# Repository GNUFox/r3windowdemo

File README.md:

# Realraum Window Demo

Responsive VGA based Demo for the Realraum Window front

## TL;DR
 * Detect people walking by through Radar Sensors (10 GHz)
 * Enable Screens only when so. is walking by to reduce power consumption
 * Use Raspberry Pi Pico(s) to run VGA based demos / intros
 * Maybe also use normal Raspberry Pi (1,2, etc.) to display other info

## TODO

- [ ] Pico <-> VGA Adapter
- [ ] Radar detector (switch power for screens)
- [ ] Normal raspberry with HDMI <-> VGA for other info

## Sources

Pico KiCAD symbol / footprint: https://forum.kicad.info/t/are-there-pi-pico-library-files-available-for-kicad-6/35844

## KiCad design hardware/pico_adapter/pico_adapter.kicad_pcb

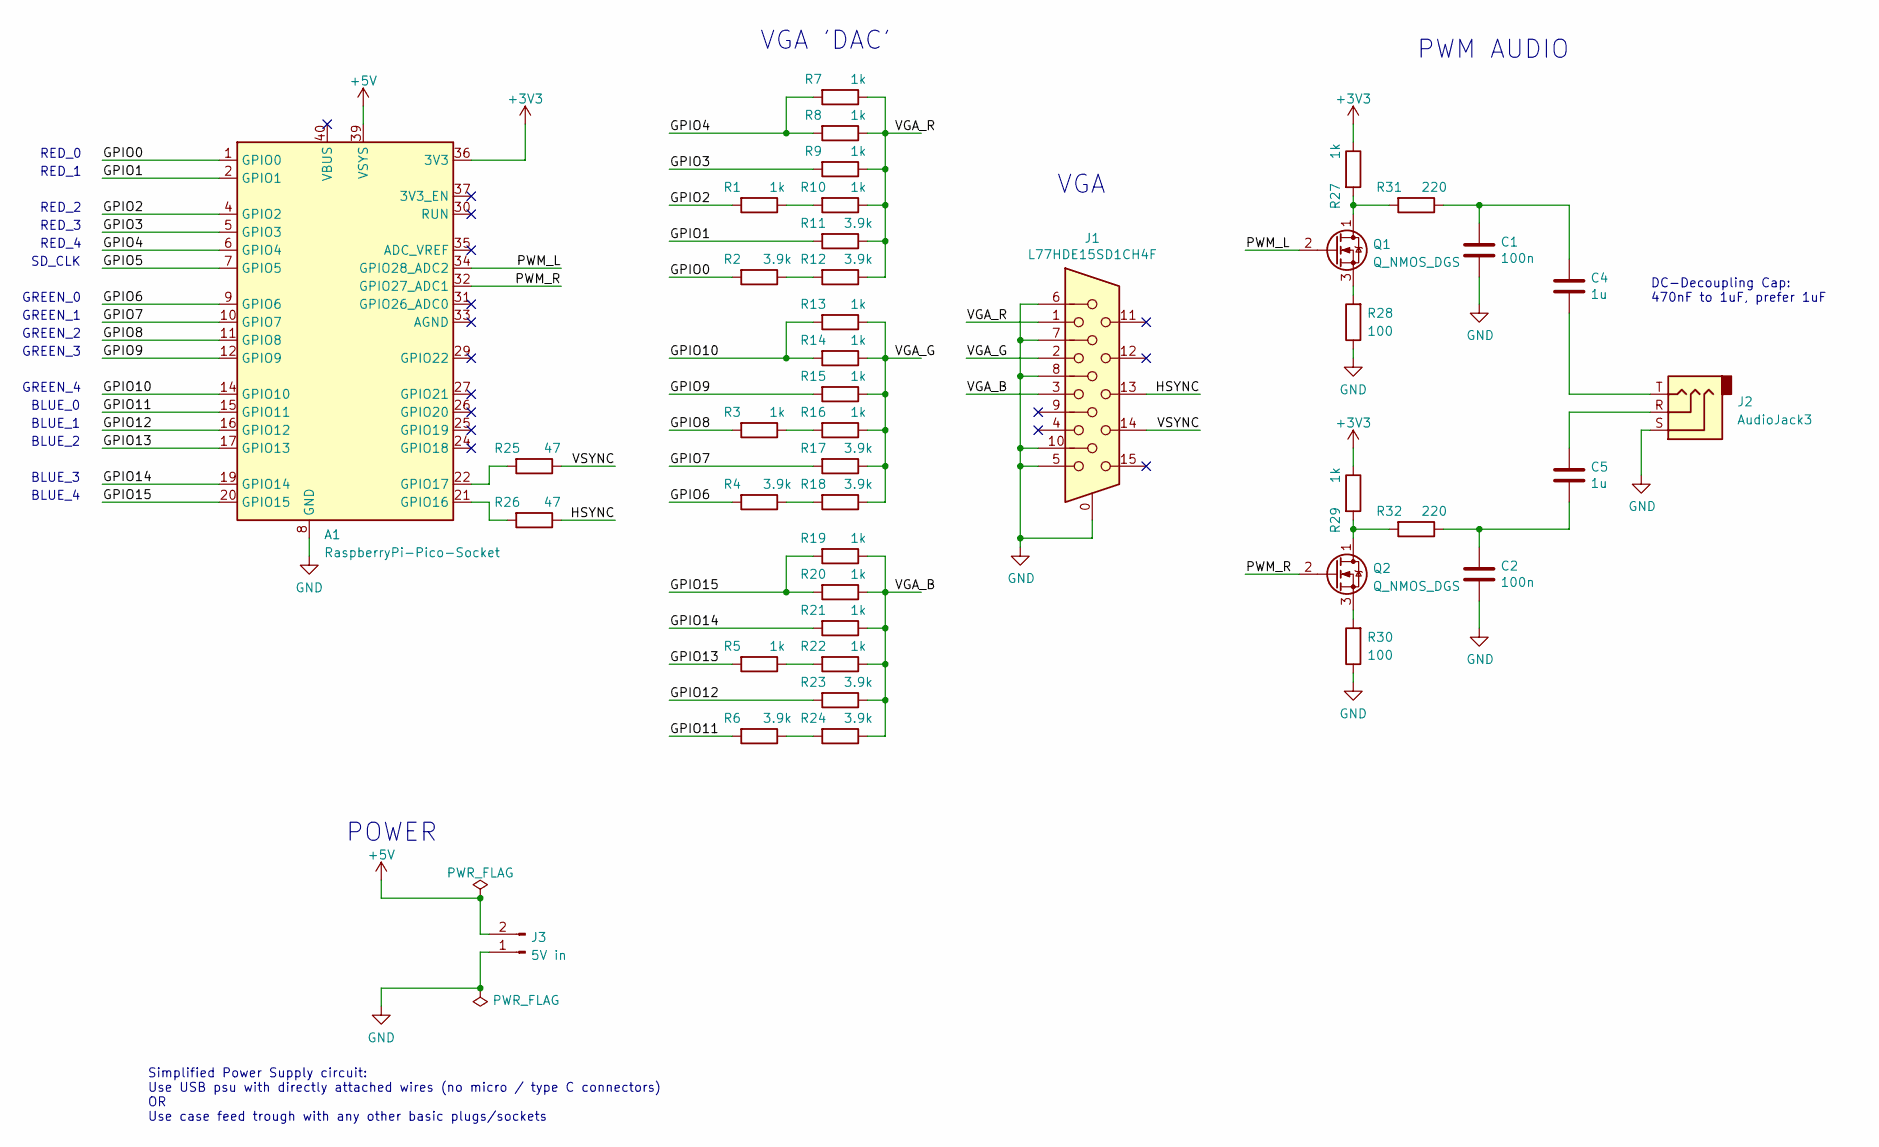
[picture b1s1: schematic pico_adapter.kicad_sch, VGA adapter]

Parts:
A1: RaspberryPi-Pico-Socket; Raspberry_Pi_Pico_Socket
C1, C2: 100n; C_Rect_L7.5mm_W6.5mm_P5.00mm
C4, C5: 1u; C_Rect_L7.5mm_W6.5mm_P5.00mm
J1: L77HDE15SD1CH4F; DSUB-15-HD_Female_Horizontal_P2.29x1.98mm_EdgePinOffset8.35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
J2: AudioJack3; Jack_3.5mm_CUI_SJ1-3533NG_Horizontal
J3: 5V in; PinHeader_1x02_P2.54mm_Vertical
Q1, Q2: Q_NMOS_DGS; TO-92_Wide
R1, R3, R5, R7, R8, R9, R10, R13, R14, R15, R16, R19, R20, R21, R22, R27, R29: 1k; R_Axial_DIN0207_L6.3mm_D2.5mm_P10.16mm_Horizontal
R2, R4, R6, R11, R12, R17, R18, R23, R24: 3.9k; R_Axial_DIN0207_L6.3mm_D2.5mm_P10.16mm_Horizontal
R25, R26: 47; R_Axial_DIN0207_L6.3mm_D2.5mm_P10.16mm_Horizontal
R28, R30: 100; R_Axial_DIN0207_L6.3mm_D2.5mm_P10.16mm_Horizontal
R31, R32: 220; R_Axial_DIN0207_L6.3mm_D2.5mm_P10.16mm_Horizontal

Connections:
+3V3: A1.36 (3V3), R27.1, R29.1; also elsewhere on the board
/3V3_EN: A1.37 (3V3_EN); also elsewhere on the board
/ADC_VREF: A1.35 (ADC_VREF); also elsewhere on the board
/AGND: A1.33 (AGND); also elsewhere on the board
/GPIO0: A1.1 (GPIO0), R2.2
/GPIO1: A1.2 (GPIO1), R11.2
/GPIO2: A1.4 (GPIO2), R1.2
/GPIO3: A1.5 (GPIO3), R9.2
/GPIO4: A1.6 (GPIO4), R7.2, R8.2
/GPIO5: A1.7 (GPIO5)
/GPIO6: A1.9 (GPIO6), R4.2
/GPIO7: A1.10 (GPIO7), R17.2
/GPIO8: A1.11 (GPIO8), R3.2
/GPIO9: A1.12 (GPIO9), R15.2
/GPIO10: A1.14 (GPIO10), R13.2, R14.2
/GPIO11: A1.15 (GPIO11), R6.2
/GPIO12: A1.16 (GPIO12), R23.2
/GPIO13: A1.17 (GPIO13), R5.2
/GPIO14: A1.19 (GPIO14), R21.2
/GPIO15: A1.20 (GPIO15), R19.2, R20.2
/GPIO16: A1.21 (GPIO16), R26.2
/GPIO17: A1.22 (GPIO17), R25.2
/GPIO18: A1.24 (GPIO18); also elsewhere on the board
/GPIO19: A1.25 (GPIO19); also elsewhere on the board
/GPIO20: A1.26 (GPIO20); also elsewhere on the board
/GPIO21: A1.27 (GPIO21); also elsewhere on the board
/GPIO22: A1.29 (GPIO22); also elsewhere on the board
/GPIO26: A1.31 (GPIO26_ADC0); also elsewhere on the board
/HSYNC: J1.13, R26.1
/PWM_L: A1.34 (GPIO28_ADC2), Q1.2 (G)
/PWM_R: A1.32 (GPIO27_ADC1), Q2.2 (G)
/RUN: A1.30 (RUN); also elsewhere on the board
/VBUS: A1.40 (VBUS); also elsewhere on the board
/VGA_B: J1.3, R19.1, R20.1, R21.1, R22.1, R23.1, R24.1
/VGA_G: J1.2, R13.1, R14.1, R15.1, R16.1, R17.1, R18.1
/VGA_R: J1.1, R7.1, R8.1, R9.1, R10.1, R11.1, R12.1
/VSYNC: J1.14, R25.1
GND: A1.3 (GND), A1.8 (GND), A1.13 (GND), A1.18 (GND), A1.23 (GND), A1.28 (GND), A1.38 (GND), C1.2, C2.2, J1.0, J1.5, J1.6, J1.7, J1.8, J1.10, J2.S, J3.1, R28.1, R30.1; also elsewhere on the board
unnamed 39: A1.39 (VSYS), J3.2; also elsewhere on the board
unnamed: C1.1, C4.1, R31.1
unnamed: C2.1, C5.2, R32.1
unnamed: C4.2, J2.T
unnamed: C5.1, J2.R
unnamed: Q1.1 (D), R27.2, R31.2
unnamed: Q1.3 (S), R28.2
unnamed: Q2.1 (D), R29.2, R32.2
unnamed: Q2.3 (S), R30.2
unnamed: R1.1, R10.2
unnamed: R2.1, R12.2
unnamed: R3.1, R16.2
unnamed: R4.1, R18.2
unnamed: R5.1, R22.2
unnamed: R6.1, R24.2

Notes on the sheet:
DC-Decoupling Cap: 470nF to 1uF, prefer 1uF
POWER
PWM AUDIO
SD_CLK
RED_2
GREEN_3
RED_4
BLUE_3
GREEN_4
BLUE_4
GREEN_2
GREEN_0
RED_3
VGA 'DAC'
Simplified Power Supply circuit: Use USB psu with directly attached wires (no micro / type C connectors) OR Use case feed trough with any other basic plugs/sockets
GREEN_1
BLUE_2
RED_1
BLUE_1
BLUE_0
RED_0
VGA

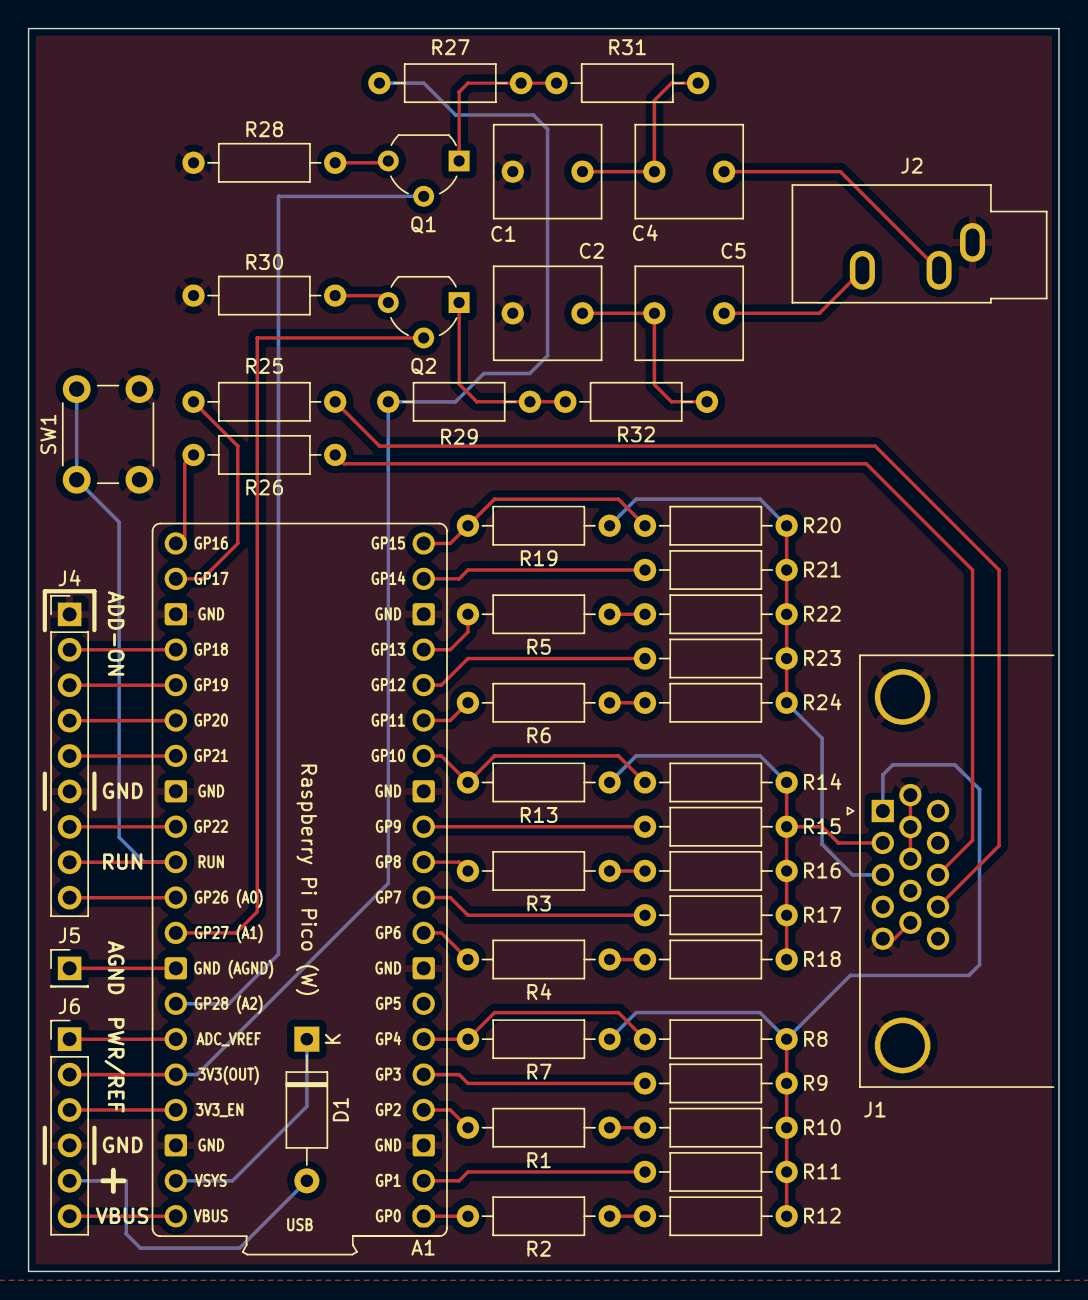
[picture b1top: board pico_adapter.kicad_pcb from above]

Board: 2 copper layers, 73.9 x 89.2 mm, 46 parts (0 on the bottom side), 53 nets.

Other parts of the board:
D1: D_Schottky; D_A-405_P10.16mm_Horizontal
J4: ADD-ON; PinHeader_1x09_P2.54mm_Vertical
J5: AGND; PinHeader_1x01_P2.54mm_Vertical
J6: PWR_REF; PinHeader_1x06_P2.54mm_Vertical
SW1: SW_Push; SW_PUSH_6mm_H5mm

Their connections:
+3V3: J6.2; also elsewhere on the board
+5V: D1.2 (A), J6.5
/3V3_EN: J6.3; also elsewhere on the board
/ADC_VREF: J6.1; also elsewhere on the board
/AGND: J5.1; also elsewhere on the board
/GPIO18: J4.2; also elsewhere on the board
/GPIO19: J4.3; also elsewhere on the board
/GPIO20: J4.4; also elsewhere on the board
/GPIO21: J4.5; also elsewhere on the board
/GPIO22: J4.7; also elsewhere on the board
/GPIO26: J4.9; also elsewhere on the board
/RUN: J4.8, SW1.1; also elsewhere on the board
/VBUS: J6.6; also elsewhere on the board
GND: J4.1, J4.6, J6.4, SW1.2; also elsewhere on the board
unnamed 39: D1.1 (K); also elsewhere on the board

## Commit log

2022-09-17 initial
2022-09-17 started simplified demo board
2022-09-18 added gitignore + Power section
2022-09-26 added DC decoupling on output
2022-09-27 added footprints + assigned footprints + minor changes
2022-09-27 added a few ideas
2022-10-12 fixed library for pico socket
2022-10-12 simplified PSU only via USB
2022-10-13 fixed PWR_FLAG in schematic, problem: layout GND area does not fill
2022-10-13 GND area does fill now, still DRC errors
2022-10-13 changed 3.5mm socket
2022-10-13 UPDATED PICO FOOTPRINT [!] + smaller board
2022-10-14 added first idea for radar IF amplifier
2022-10-14 bigger resistors
2022-10-15 added addon-headers + reset button
2022-10-19 added notes
